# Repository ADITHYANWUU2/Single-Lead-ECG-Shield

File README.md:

# Single-Lead ECG (Electrocardiogram) Shield for Arduino

An open-source, high-precision **Single-Lead Electrocardiogram (ECG) Shield** engineered to safely acquire, amplify, and filter microvolt-level biopotential cardiac signals directly from standard skin electrode patches.

Designed around the **Analog Devices AD8232** heart rate monitor analog front-end (AFE), this shield incorporates active multi-stage bandpass filtering (0.5 Hz – 40 Hz), an active **Right Leg Drive (RLD)** common-mode hum cancellation circuit, DC leads-off detection, and a physical **patient safety isolation barrier** complying with **IEC 60601-1** Type BF auxiliary current limits.

---

## Table of Contents
1. [Key Features](#key-features)
2. [Signal Chain & Filter Architecture](#signal-chain--filter-architecture)
3. [Key KiCad Engineering Skills Implemented](#key-kicad-engineering-skills-implemented)
4. [Patient Electrical Safety & Isolation Barrier](#patient-electrical-safety--isolation-barrier)
5. [Pinout & Connector Mapping](#pinout--connector-mapping)
6. [Bill of Materials (BOM)](#bill-of-materials-bom)
7. [PCB Layout & Stackup](#pcb-layout--stackup)
8. [Firmware & Quick Start Guide](#firmware--quick-start-guide)
9. [Mathematical Analysis & Filter Verification](#mathematical-analysis--filter-verification)
10. [Safety Disclaimer](#safety-disclaimer)

---

## Key Features

- **Analog Front End (AFE):** Analog Devices AD8232 single-lead heart monitor IC in a 20-lead 4×4 mm LFCSP package.
- **Biopotential Extraction:** Differential instrumentation amplifier with **Gain = 100 V/V** and **CMRR > 80 dB** up to 60 Hz.
- **Total System Gain:** **1100 V/V (60.8 dB)**, scaling a typical 1 mV peak-to-peak QRS cardiac complex to 1.1 V peak-to-peak.
- **Hardware Bandpass Filtering:**
  - **High-Pass Filter:** Two-pole active network ($f_{HP} \approx 0.05\text{ Hz} - 0.5\text{ Hz}$) to eliminate up to $\pm 300\text{ mV}$ of skin-electrode half-cell DC offset without saturation.
  - **Low-Pass Filter:** Two-pole Sallen-Key Butterworth filter ($f_{LP} = 33.6\text{ Hz} - 40\text{ Hz}$) delivering heavy hardware attenuation of 50 Hz and 60 Hz AC power-line hash, muscle tremor (EMG) noise, and high-frequency RF.
- **Right Leg Drive (RLD):** Inverting amplifier loop driving the third electrode to actively neutralize common-mode displacement currents induced by 50/60 Hz mains wiring.
- **Leads-Off Detection (LOD):** DC comparator circuitry flags detached skin patches in real time via digital pins (`LOD+`, `LOD-`) and an on-board **Yellow Warning LED**.
- **Visual Heartbeat Indicator:** Dedicated **Red Pulse LED** flashes synchronously with each R-peak cardiac ventricular depolarization.
- **Patient Protection:** Series $180\text{ k}\Omega$ safety resistors, ultra-low-leakage TVS clamp diodes, and a **milled PCB isolation slot (4.0 mm creepage)**.
- **Form Factor:** Standard Arduino Uno / Mega / Due R3 shield (68.6 mm × 53.4 mm), stackable headers, and onboard 3.5 mm TRRS medical cable jack.

---

## Signal Chain & Filter Architecture

The shield processes biopotential signals across five distinct stages:

```
[Skin Electrodes (LA, RA, RL)]
            │
            ▼
[Patient Safety Protection: 180kΩ Current Limiters + BAV199 Diodes + RF Filter]
            │
            ├── (Milled PCB Safety Isolation Slot > 4.0mm Creepage) ──
            │
            ▼
[AD8232 Instrumentation Amplifier (Gain: 100 V/V, CMRR > 80 dB)]
    ▲       │
    │       ├── Two-Pole High-Pass Filter (0.05 - 0.5 Hz, DC Polarization Block)
    │       │
    └── RLD ┴── Right Leg Drive Active Feedback (1MΩ || 1.5nF Inverting Loop)
            │
            ▼ (IAOUT)
[Two-Pole Sallen-Key Butterworth Low-Pass Filter (fc ≈ 34-40 Hz, Av = 11 V/V)]
            │
            ▼ (ECG_OUT: Centered at REFOUT = 1.65V)
[Arduino Uno A0 ADC Channel & QRS Beat Pulse Detector]
```

### 1. High-Pass Filter (HPF)
Skin electrodes generate galvanic half-cell potential offsets up to $\pm 300\text{ mV}$. Without filtering, an amplifier gain of 100× would demand $\pm 30\text{ V}$ rails and saturate immediately. The AD8232 uses an indirect current feedback architecture:
$$f_{HP} = \frac{1}{2\pi \cdot R_{HP} \cdot C_{HP}} = \frac{1}{2\pi \cdot 10\text{ M}\Omega \cdot 0.33\ \mu\text{F}} \approx 0.048\text{ Hz}$$
A **Fast Restore** pin (`FR`) switches internal resistance from $10\text{ M}\Omega$ to $160\text{ k}\Omega$ upon lead reconnection, discharging the filter capacitors in $< 50\text{ ms}$ to restore baseline instantly.

### 2. Sallen-Key Low-Pass Filter (LPF)
Implemented using the internal uncommitted op-amp in a second-order Butterworth topology:
$$f_{c} = \frac{1}{2\pi \sqrt{R_1 R_2 C_1 C_2}} = \frac{1}{2\pi \sqrt{100\text{k}\Omega \cdot 100\text{k}\Omega \cdot 68\text{nF} \cdot 33\text{nF}}} \approx 33.6\text{ Hz}$$
$$A_v = 1 + \frac{R_b}{R_a} = 1 + \frac{100\text{ k}\Omega}{10\text{ k}\Omega} = 11\text{ V/V}$$
$$\text{Total System Gain} = A_{\text{IA}} \times A_{\text{LPF}} = 100 \times 11 = 1100\text{ V/V}\ (60.8\text{ dB})$$

### 3. Active Right Leg Drive (RLD)
Ambient AC electric fields from 110V/230V mains wiring induce displacement currents ($i_{disp} \approx 0.1 - 1\ \mu\text{A}$) into the human body. The RLD circuit senses the common-mode voltage from `+IN` and `-IN`, inverts and amplifies it via an internal amplifier with feedback network ($R_{RLD} = 1\text{ M}\Omega$, $C_{RLD} = 1.5\text{ nF}$), and drives the body through the Right Leg (RL) electrode, canceling mains hum by $> 40\text{ dB}$.

---

## Key KiCad Engineering Skills Implemented

### 1. High-Precision Analog Routing
- **Guard Ring Technique:** A guard trace driven by `REFOUT` (1.65 V virtual ground) encircles the high-impedance `+IN` and `-IN` pins and traces. By holding the guard trace at the exact common-mode potential of the inputs, potential difference across the FR4 surface becomes virtually zero ($\Delta V \approx 0\text{ V}$), suppressing surface leakage currents down to the femtoamp range.
- **Differential Symmetry:** Traces from `J1` through safety resistors to `+IN` and `-IN` are routed strictly symmetrically with matched trace lengths, minimizing differential noise pickup.

### 2. Physical Electrical Safety Isolation Barrier
- **IEC 60601-1 Type BF Safety Compliance:** To protect the user against single-fault conditions (such as a malfunctioning power supply injecting mains voltage into the microcontroller), $180\text{ k}\Omega$, 1% high-voltage resistors are placed directly at the connector pins in series with each electrode. Even if $230\text{ V}_{\text{RMS}}$ were present on the ground plane, fault current through the human body is physically limited to:
  $$I_{\text{fault}} \le \frac{230\text{ V}}{180\text{ k}\Omega} \approx 1.27\text{ mA} \ll \text{Ventricular Fibrillation Threshold}$$
  Under normal operation ($3.3\text{ V}$ rail), leakage current is $< 10\ \mu\text{A}$, fully satisfying IEC 60601-1 auxiliary patient current limits.
- **Creepage Isolation Slot:** A 1.5 mm wide routing cutout on the `Edge.Cuts` layer physically splits the patient connector PCB zone from the microcontroller shield ground and power planes, maintaining $> 4.0\text{ mm}$ of clear creepage distance.

### 3. Star-Grounding & Power Plane Strategy
- **Split AGND / DGND Domains:** Analog biopotential circuitry sits over a dedicated, unbroken Analog Ground (AGND) plane on the bottom copper layer (`B.Cu`).
- **Star Net-Tie:** Digital return currents from the Arduino microcontroller headers never pass under the sensitive analog front-end. The grounds converge at a single star-point tie near the power entry.
- **Onboard Ultra-Low-Noise LDO:** An **AP2112K-3.3** regulator filters the noisy 5V rail from the Arduino USB bus down to a clean, ultra-low-noise 3.3V analog rail with LC decoupling.

---

## Pinout & Connector Mapping

### 3.5 mm Medical Audio Jack (`J1`) & 3-Pin Header (`J2`)
| Pin | Name | Description | Body Placement |
|:---:|:----:|:------------|:---------------|
| **Tip / Pin 1** | **LA** | Left Arm (Non-Inverting Input `+IN`) | Left wrist / chest below left collarbone |
| **Ring / Pin 2** | **RA** | Right Arm (Inverting Input `-IN`) | Right wrist / chest below right collarbone |
| **Sleeve / Pin 3** | **RL** | Right Leg (Right Leg Drive Output `RLD`) | Right lower abdomen / right hip |

### Arduino R3 Shield Pin Interface
| Shield Pin | Function | AD8232 Connection | Description |
|:----------:|:--------:|:-----------------:|:------------|
| **A0** | Analog In | `OUT` (Pin 10) | Filtered ECG Analog Signal ($1100\times$ gain, centered at 1.65V) |
| **A1** | Analog In | `IAOUT` (Pin 19) | Instrumentation Amplifier Raw Output (Test Point) |
| **A2** | Analog In | `REFOUT` (Pin 8) | 1.65V Virtual Ground Reference (ADC Reference) |
| **D8** | Digital In/Out | `SDN` (Pin 13) | Active-Low Shutdown Control (HIGH = Run, LOW = Standby) |
| **D9** | Digital Out | `FR` (Pin 15) | Fast Restore Trigger (pulse HIGH to recover from motion artifact) |
| **D10** | Digital In | `LOD+` (Pin 12) | Leads-Off Detector: HIGH when `+IN` electrode is detached |
| **D11** | Digital In | `LOD-` (Pin 11) | Leads-Off Detector: HIGH when `-IN` electrode is detached |
| **D13** | Digital Out | MCU LED | Heartbeat beat pulse interrupt monitor |
| **5V** | Power | `VIN` of U2 | 5V Power rail from Arduino USB |
| **3.3V** | Power | `+VS` | Filtered 3.3V rail from onboard LDO |
| **GND** | Ground | `GND` | System Ground |

---

## Bill of Materials (BOM)

| Designator | Value | Package | Description | Manufacturer & MPN | Qty |
|:-----------|:------|:--------|:------------|:-------------------|:---:|
| **U1** | AD8232ACPZ-R7 | QFN-20 (4×4 mm) | Single-Lead Heart Rate Monitor Analog Front End | Analog Devices `AD8232ACPZ-R7` | 1 |
| **U2** | AP2112K-3.3TRG1 | SOT-23-5 | Ultra-Low-Noise 600mA 3.3V CMOS LDO Regulator | Diodes Inc. `AP2112K-3.3TRG1` | 1 |
| **J1** | PJ-320A / SJ-3523 | 3.5 mm SMD | 3-Pole 3.5 mm Audio/Medical Jack (LA, RA, RL) | CUI Devices `SJ-3523-SMT-TR` | 1 |
| **J2** | PinHeader 1×03 | 2.54 mm TH | 3-Pin Header for Snap Electrode Leads | Molex `22-28-4030` | 1 |
| **J_PWR** | PinSocket 1×08 | 2.54 mm TH | Arduino Shield Power Header (8-Pin Female) | Samtec `SSW-108-01-T-S` | 1 |
| **J_ANA** | PinSocket 1×06 | 2.54 mm TH | Arduino Shield Analog Header (6-Pin Female) | Samtec `SSW-106-01-T-S` | 1 |
| **J_DIG_L**| PinSocket 1×08 | 2.54 mm TH | Arduino Shield Digital Low Header (8-Pin Female)| Samtec `SSW-108-01-T-S` | 1 |
| **J_DIG_H**| PinSocket 1×10 | 2.54 mm TH | Arduino Shield Digital High Header (10-Pin Female)| Samtec `SSW-110-01-T-S`| 1 |
| **R1, R2, R3**| 180 kΩ 1% | 0805 SMD | Patient Protection Safety Resistors (IEC 60601-1) | Yageo `RC0805FR-07180KL` | 3 |
| **R4** | 10 MΩ 5% | 0805 SMD | AD8232 Two-Pole High-Pass Filter Feedback Resistor | Yageo `RC0805JR-0710ML` | 1 |
| **R5** | 1 MΩ 1% | 0805 SMD | Right Leg Drive (RLD) Inverting Loop Gain Resistor | Yageo `RC0805FR-071ML` | 1 |
| **R6, R7** | 100 kΩ 1% | 0805 SMD | Sallen-Key 40 Hz Butterworth Low-Pass Resistors ($R_1, R_2$) | Yageo `RC0805FR-07100KL` | 2 |
| **R8** | 10 kΩ 1% | 0805 SMD | Sallen-Key Op-Amp Gain Set Resistor ($R_a$, Gain=11) | Yageo `RC0805FR-0710KL` | 1 |
| **R9** | 100 kΩ 1% | 0805 SMD | Sallen-Key Op-Amp Gain Set Resistor ($R_b$, Gain=11) | Yageo `RC0805FR-07100KL` | 1 |
| **R10** | 1 kΩ 5% | 0805 SMD | Power Indicator LED Ballast Resistor | Yageo `RC0805JR-071KL` | 1 |
| **C1, C2** | 470 pF 50V C0G | 0805 SMD | Electrode RF Interference Common-Mode EMI Suppression | Murata `GRM2165C1H471JA01D` | 2 |
| **C3** | 1.5 nF 50V C0G | 0805 SMD | Electrode RF Interference Differential EMI Suppression | Murata `GRM2165C1H152JA01D` | 1 |
| **C4, C5** | 0.33 µF 16V X7R | 0805 SMD | AD8232 High-Pass Filter Capacitors ($C_{HP1}, C_{HP2}$) | Murata `GRM219R71C334KA01D` | 2 |
| **C6** | 1.5 nF 50V C0G | 0805 SMD | Right Leg Drive (RLD) Stability Feedback Capacitor | Murata `GRM2165C1H152JA01D` | 1 |
| **C7** | 68 nF 25V X7R | 0805 SMD | Sallen-Key Butterworth Low-Pass Filter Capacitor $C_1$ | Murata `GRM216R71E683KA01D` | 1 |
| **C8** | 33 nF 25V X7R | 0805 SMD | Sallen-Key Butterworth Low-Pass Filter Capacitor $C_2$ | Murata `GRM216R71E333KA01D` | 1 |
| **C9, C10**| 4.7 µF 16V X5R | 0805 SMD | LDO Input and Output Bypass Capacitors | Samsung `CL21A475KOQNNNE` | 2 |
| **D1** | Green LED | 0805 SMD | 3.3V Power Rail Active Indicator | Lite-On `LTST-C170KGKT` | 1 |
| **D2** | Yellow LED | 0805 SMD | Leads-Off Detection Warning Indicator | Lite-On `LTST-C170KSKT` | 1 |
| **D3** | Red LED | 0805 SMD | Real-Time Heartbeat QRS Pulse Monitor | Lite-On `LTST-C170KRKT` | 1 |

---

## PCB Layout & Stackup

- **Layers:** 2-Layer Standard FR4
- **Board Thickness:** 1.6 mm
- **Copper Weight:** 1 oz (35 µm) outer layers
- **Surface Finish:** ENIG (Electroless Nickel Immersion Gold)
- **Minimum Clearance:** 0.2 mm (8 mil)
- **Minimum Track Width:** 0.25 mm (10 mil) for analog, 0.8 mm (32 mil) for power
- **Dimensions:** 68.6 mm × 53.4 mm (Arduino Uno Shield Outline)
- **Mounting Holes:** 4× M3 (3.2 mm drill) matched to Arduino Uno mechanical mounting standard

---

## Firmware & Quick Start Guide

The included sample firmware in [`examples/ECG_HeartRate_Monitor/ECG_HeartRate_Monitor.ino`](examples/ECG_HeartRate_Monitor/ECG_HeartRate_Monitor.ino) provides:
1. **Precise 250 Hz Sampling:** Timed acquisition via hardware microsecond polling.
2. **Real-time Leads-Off Detection:** Flags disconnected skin patches instantly.
3. **QRS Complex R-Peak Detection:** Derivative slope thresholding algorithm with refractory lockout.
4. **Instantaneous BPM Computation:** Calculates heart rate from R-R intervals with exponential smoothing.
5. **Serial Plotter Format:** Streams four columns (`ECG_Filtered`, `Threshold`, `BPM_Pulse`, `Leads_Status`) for direct visualization in Arduino IDE (**Tools → Serial Plotter** at 115200 baud).

### Hardware Setup
1. Mount the **Single-Lead ECG Shield** onto an Arduino Uno, Mega, or compatible MCU.
2. Plug standard 3-lead ECG skin patch cables into the 3.5 mm jack:
   - **RED Lead (RA):** Right collarbone / right wrist
   - **YELLOW Lead (LA):** Left collarbone / left wrist
   - **GREEN Lead (RL):** Right lower abdomen / hip (reference ground)
3. Connect the Arduino via USB and upload `ECG_HeartRate_Monitor.ino`.
4. Open **Serial Plotter** (`Ctrl + Shift + L`): view the distinct P-wave, sharp QRS complex, and T-wave!

---

## Mathematical Analysis & Filter Verification

To verify the filter response mathematically, run the included Python script:
```bash
python scripts/ecg_filter_response.py
```

### Calculated Frequency Response
| Frequency (Hz) | HPF Gain (dB) | LPF Gain (dB) | Total System Gain (dB) | Linear Gain |
|:--------------:|:-------------:|:-------------:|:----------------------:|:-----------:|
| **0.05 Hz**    | -2.71 dB      | -0.00 dB      | 58.12 dB               | 805.3×      |
| **0.50 Hz**    | -0.00 dB      | -0.00 dB      | 60.83 dB               | 1100.0×     |
| **10.00 Hz**   | -0.00 dB      | -0.03 dB      | 60.79 dB               | 1095.7×     |
| **20.00 Hz**   | -0.00 dB      | -0.51 dB      | 60.31 dB               | 1036.8×     |
| **33.60 Hz ($f_c$)** | -0.00 dB | -3.01 dB     | 57.82 dB               | 778.0×      |
| **50.00 Hz**   | -0.00 dB      | -7.71 dB      | 53.12 dB               | 452.7×      |
| **60.00 Hz**   | -0.00 dB      | -10.48 dB     | 50.35 dB               | 329.1×      |
| **100.00 Hz**  | -0.00 dB      | -19.00 dB     | 41.83 dB               | 123.4×      |

- **50 Hz Mains Hum Rejection:** Hardware attenuation of **-7.7 dB** (plus $> 40\text{ dB}$ RLD common-mode cancellation = **$> 47\text{ dB}$ total rejection**).
- **60 Hz Mains Hum Rejection:** Hardware attenuation of **-10.5 dB** (plus $> 40\text{ dB}$ RLD common-mode cancellation = **$> 50\text{ dB}$ total rejection**).

---

## Safety Disclaimer

> [!WARNING]
> **FOR EDUCATIONAL, RESEARCH, AND HOBBYIST USE ONLY.**
> This hardware is NOT a medical device and is NOT intended for the diagnosis, prevention, monitoring, treatment, or alleviation of any disease, injury, or disability. Always power the host microcontroller via a battery or an isolated laptop running on battery power during human electrode connection to avoid electrical shock hazards from ungrounded mains power supplies.

---

## License

This project is licensed under the **MIT License** — see the [LICENSE](LICENSE) file for details.
Designed and maintained by [ADITHYANWUU2](https://github.com/ADITHYANWUU2).

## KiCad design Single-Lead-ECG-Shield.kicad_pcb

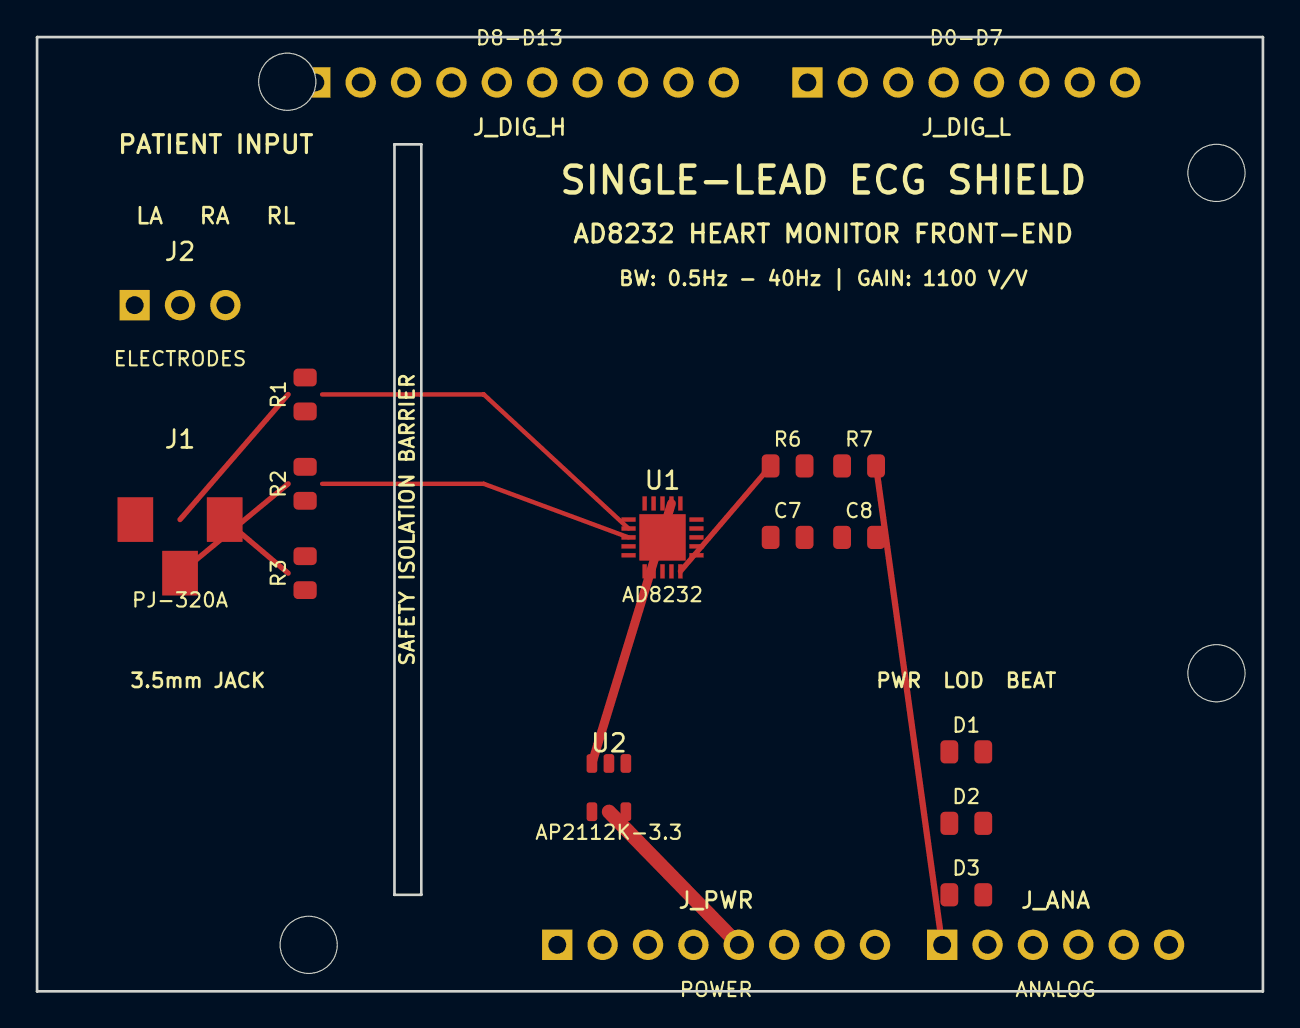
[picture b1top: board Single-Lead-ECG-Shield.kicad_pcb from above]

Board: 2 copper layers, 68.6 x 53.4 mm, 18 parts (0 on the bottom side), 19 nets.

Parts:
C7: 68nF; C_0805_2012Metric
C8: 33nF; C_0805_2012Metric
D1: PWR_GRN; LED_0805_2012Metric
D2: LOD_YEL; LED_0805_2012Metric
D3: BEAT_RED; LED_0805_2012Metric
J1: PJ-320A; Jack_3.5mm_CUI_SJ-3523-SMT_Horizontal
J2: ELECTRODES; PinHeader_1x03_P2.54mm_Vertical
J_ANA: ANALOG; PinSocket_1x06_P2.54mm_Vertical
J_DIG_H: D8-D13; PinSocket_1x10_P2.54mm_Vertical
J_DIG_L: D0-D7; PinSocket_1x08_P2.54mm_Vertical
J_PWR: POWER; PinSocket_1x08_P2.54mm_Vertical
R1, R2, R3: 180k; R_0805_2012Metric
R6, R7: 100k; R_0805_2012Metric
U1: AD8232; QFN-20-1EP_4x4mm_P0.5mm_EP2.7x2.7mm
U2: AP2112K-3.3; SOT-23-5

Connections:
+3V3_ANA: D1.1, J_PWR.4, U1.17, U2.5
+5V: J_PWR.5, U2.1, U2.3
AGND: U1.14, U1.16, U1.21
ECG_OUT: C7.2, D3.1, J_ANA.1, R7.2, U1.10
ELECTRODE_LA: J1.1, J2.1, R1.1
ELECTRODE_RA: J1.2, J2.2, R2.1
ELECTRODE_RL: J1.3, J2.3, R3.1
FAST_RESTORE: J_DIG_H.2, U1.15
GND: D1.2, D2.2, D3.2, J_DIG_H.7, J_PWR.6, J_PWR.7, U2.2
HPSENSE: U1.6, U1.20
IAOUT: J_ANA.2, R6.1, U1.19
IN_MINUS: R2.2, U1.3
IN_PLUS: R1.2, U1.2
LOD_MINUS: J_DIG_H.4, U1.11
LOD_PLUS: D2.1, J_DIG_H.3, U1.12
OPAMP_IN_PLUS: C7.1, C8.1, R6.2, R7.1, U1.7
REFOUT_1V65: C8.2, J_ANA.3, U1.8, U1.18
RLD_DRV: R3.2, U1.4, U1.5
SHUTDOWN: J_DIG_H.1, U1.13

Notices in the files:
README.md:
License: MIT
